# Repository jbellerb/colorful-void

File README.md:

# Colorful Void

This is a monorepo for "colorful void", a work-in-progress smart accent light built from a recycled monitor's backlight assembly. See each folder for specific instructions about each component.

## Usage

At it's core, this project is an internet connected light, controllable with a simple JSON-based REST API. The lights in the panel are connected to a Raspberry Pi Zero W running [void-client](void-client/), which exposes an internal control API. While this API is designed to be platform-agnostic, the client is intended to be used with [void-server](void-server/), a relay server that allows the Google Smart Home platform to communicate with the light.

## Security

The void-client API is unsecured and should **never** be exposed to the public internet. While security was a goal of both programs, attack surface mitigation is always helpful—especially since void-client is running as root. If possible, run void-client and void-server on different machines and make sure the Raspberry Pi cannot be accessed from the internet. A VPN solution like Wireguard should be used to enable communication between the two machines.

## Google Smart Home Setup

Usage with the Google Smart Home platform is functional, but some usability aspects are incomplete, such as the lack of a proper login form and requiring a full setup every time void-server is restarted. These steps assume void-client is built and running on a Pi, void-server is built and running on a publically accessable domain with HTTPS, and there is some way for the two to talk (such as a Wireguard tunnel)

### Action Setup

First you must create an Actions on Google project. This is covered in steps 1-6 of [this Google Smart Home documentation page](https://developers.google.com/assistant/smarthome/develop/create#create-project). After that, click on "Account linking" in the side bar and fill out the OAuth Client Information. Client ID should be "google" and Client Secret should be whatever you set when building void-server. The Authorization URL should be `https://whatever-url-you-are-hosting-void-server-at/auth` and the Token URL is `https://whatever-url-you-are-hosting-void-server-at/token`. Finally, click on "Actions" in the side bar and set the Fulfillment URL to `https://whatever-url-you-are-hosting-void-server-at/fulfillment`.

### Logging In

To actually control the light, you need to log in using the Google Home app. In the app, tap Settings, Works with Google, and then whatever you named your Action (which should be prefixed by [test]). This will open a browser window which will 404 because I didn't bother to write a proper login endpoint. To login, you will need to rewrite the URL to another one. Given `https://whaterver-url-you-are-hosting-void-server-at/auth?...&state={state string}&...` visit `https://oauth-redirect.googleusercontent.com/r/{your Actions project id}?code={your authorization token from building void-server}&state={state string from earlier}`. The Google Home app should open again. Follow the remaining instructions in the app and the device should be set up.

<br />

#### License

<sup>
Copyright (C) Jared Beller, 2020-2021.
</sup>
<br />
<sup>
Released under the <a href="https://www.gnu.org/licenses/gpl-3.0.txt">GNU General Public License, Version 3</a> or later. See <a href="LICENSE">LICENSE</a> for more information.
</sup>

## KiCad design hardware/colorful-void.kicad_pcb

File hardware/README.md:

# hardware

This folder contains hardware schematics and an optional controller PCB for connecting the control Raspberry Pi Zero W to the panel's WS2812 LED strip.

## Usage

The Raspberry Pi outputs at 3.3V while the WS2812 LEDs require 5V control signals, so a level shifter is needed to connect the two. For convenience, a PCB was designed to sit over the upper half of the Raspberry Pi's GPIO pins and interface between it and the LEDs. The PCB also routes power for both the LEDs and Pi, so only a single power supply is needed. Out of an abundance of caution, a 5V 4A power supply ([Adafruit product 1466](https://www.adafruit.com/product/1466)) was used to power the prototype. While the PCB is recommended for reliability, everything can also be hand-wired. When hand-wiring, pins 4-13 (excluding 7) of the SN74AHCT125 level shifter can be left disconnected. The data signal was not reliable on a breadboard, so building with one is not recommended. All components were purchased from Adafruit and are linked below.

## Bill of Materials

| Ref | Description                     | Part No.    | Adafruit PID |
| --- | ------------------------------- | ----------- | ------------ |
| J1  | Raspberry Pi Zero W Pins 1-12   | Zero W      | [3400][P1]   |
| J2  | 2-Pin 0.1" Pitch Terminal Block | KF120-2P    | [2138][P2]   |
| J3  | 3-Pin 0.1" Pitch Terminal Block | KF120-3P    | [2136][P3]   |
| U1  | Quad 3V to 5V Level-Shifter     | SN74AHCT125 | [1787][P4]   |
| R1  | 470 Ohm Resistor (1/4 Watt)     | CF1/4WXJ470 | [2781][P5]   |

[P1]: https://www.adafruit.com/product/3400
[P2]: https://www.adafruit.com/product/2138
[P3]: https://www.adafruit.com/product/2136
[P4]: https://www.adafruit.com/product/1787
[P5]: https://www.adafruit.com/product/2781

<br />

#### License

<sup>
Copyright (C) Jared Beller, 2021.
</sup>
<br />
<sup>
Released under the <a href="https://www.gnu.org/licenses/gpl-3.0.txt">GNU General Public License, Version 3</a> or later. See <a href="LICENSE">LICENSE</a> for more information.
</sup>

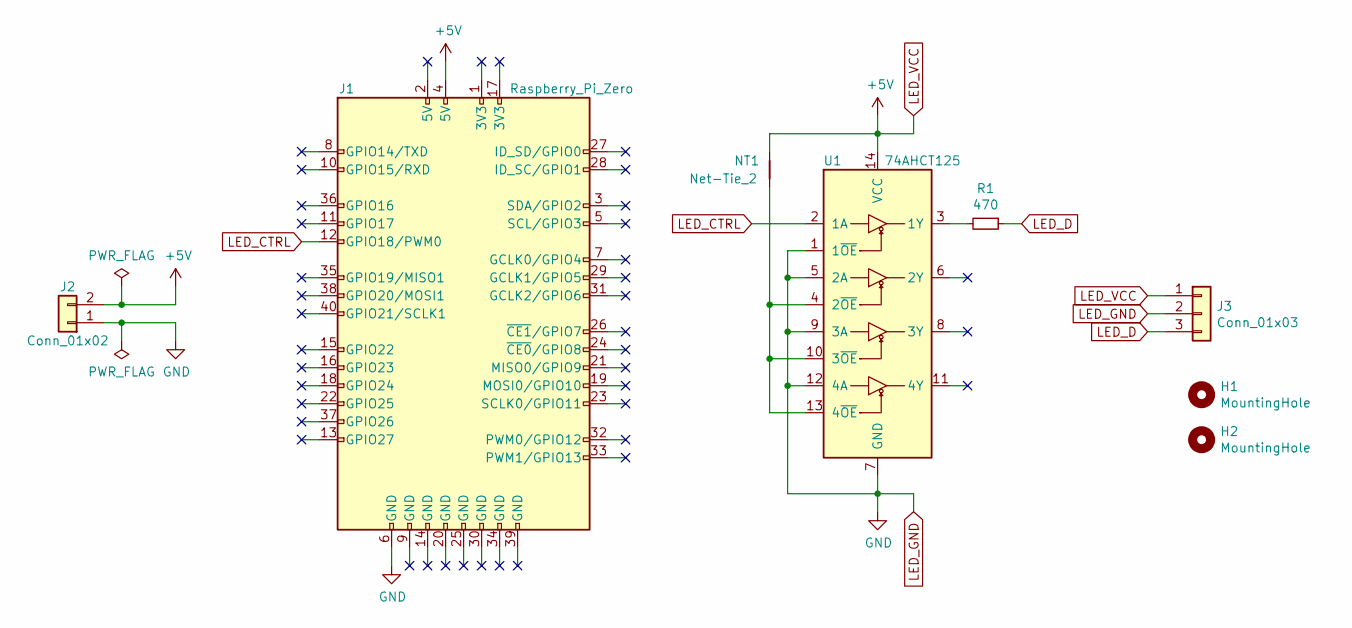
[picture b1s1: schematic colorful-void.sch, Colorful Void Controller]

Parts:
H1, H2: MountingHole; MountingHole_M2.5
J1: Raspberry_Pi_Zero; PinHeader_2x06_P2.54mm_Vertical
J2: Conn_01x02; TerminalBlock_Kaweei_1x02_P2.54mm_Horizontal
J3: Conn_01x03; TerminalBlock_Kaweei_1x03_P2.54mm_Horizontal
NT1: Net-Tie_2; NetTie-2_SMD_Pad0.5mm
R1: 470; R_Axial_DIN0309_L9.0mm_D3.2mm_P12.70mm_Horizontal
U1: 74AHCT125; DIP-14_W7.62mm

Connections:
LED_CTRL: J1.12 (GPIO18/PWM0), U1.2 (1A)
LED_D: J3.3, R1.1
LED_GND: J1.6 (GND), J2.1, J3.2, U1.1 (1~OE), U1.5 (2A), U1.7 (GND), U1.9 (3A), U1.12 (4A)
LED_VCC: J1.4 (5V), J2.2, J3.1, NT1.2, U1.14 (VCC)
unnamed: NT1.1, U1.4 (2~OE), U1.10 (3~OE), U1.13 (4~OE)
unnamed: R1.2, U1.3 (1Y)

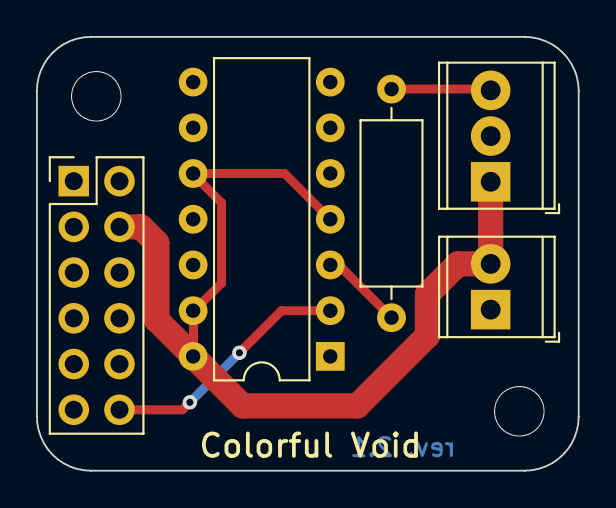
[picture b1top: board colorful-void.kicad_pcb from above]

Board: 2 copper layers, 30.1 x 24.1 mm, 8 parts (0 on the bottom side), 6 nets.

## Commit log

2020-12-13 Initial hardware revision
2020-12-13 Initial client implementation
2020-12-14 Return updated state on change request
2020-12-16 Token exchange + Client control
2020-12-18 Initial fulfillment endpoint types
2020-12-21 Initial fulfillment implementation
2020-12-24 Validate token before fulfilling
2020-12-25 Build server with Stack
2020-12-25 Fix permissions
2020-12-25 Connect client to RGB strip
2021-01-03 PCB rev. 1
2021-01-04 Write the READMEs
2021-01-10 Current limiting resistor on LED data line
2021-01-10 Minor PCB routing optimization
2021-01-23 Update Haskell copyright disclaimers to Haddock
